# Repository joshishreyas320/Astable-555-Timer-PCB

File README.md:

# Astable 555 Timer PCB

> Eagle CAD PCB Design | 2-Layer Board | NE555 + 7805

---

## Project Description
A variable-frequency astable oscillator PCB designed in **Eagle CAD** using the classic **NE555 timer IC** in astable mode. A **100kΩ potentiometer** allows real-time frequency adjustment. Input power (+12V) is regulated to +5V using a **7805 linear regulator**. An LED blinks at the output frequency for visual feedback. The board includes a DC barrel jack and a 2-pin power header for flexible power input.

**Short Description (≤350 chars):**
> Astable 555 timer PCB with variable frequency output using 100kΩ potentiometer. NE555 IC generates continuous square wave with LED indicator. 12V input regulated via 7805. Designed in Eagle CAD.

---

## Key Components

| Component | Description |
|-----------|-------------|
| **NE555** | Timer IC in astable (free-running oscillator) mode |
| **7805 (IC1)** | 5V linear voltage regulator (TO-92) |
| **R5 – 100kΩ POT** | Variable resistor for frequency tuning |
| **R1 – 10kΩ** | Timing resistor Ra |
| **R2 – 1kΩ** | Timing resistor Rb |
| **R3 – 330Ω** | LED current limiting resistor |
| **C3, C4 – 10µF** | Timing capacitor and supply filter |
| **C1, C2 – 0.1µF** | Bypass/decoupling capacitors |
| **LED1** | Output frequency visual indicator |
| **DC JACK** | 2.0mm barrel jack for power input |

---

## Design Features
- NE555 wired in astable mode for continuous square wave output
- 100kΩ potentiometer enables real-time frequency adjustment
- Frequency approximately: f = 1.44 / ((R1 + 2×R2 + POT) × C3)
- 12V DC input regulated to stable 5V via 7805 regulator
- LED blinks at oscillator frequency – instant visual verification
- Dual power input: DC barrel jack + 2-pin pin header
- All through-hole components for easy soldering and prototyping

---

## Signal Flow
```
DC Barrel Jack / JP1 Header – 12V Input
       ↓
  7805 – 5V Voltage Regulator
       ↓
  NE555 Timer IC – Astable Mode
       ↑
  R1 (10kΩ) + R2 (1kΩ) + R5 POT (100kΩ) + C3 (10µF) – RC Timing
       ↓
  Square Wave Output (Pin 3)
       ↓
  R3 (330Ω) + LED1 – Visual Output Indicator
```

---

## Files Included
- Astable_555_timer.sch – Eagle Schematic
- Astable_555_timer.brd – Eagle PCB Layout
- GERBER_FILES_Astable_555_timer_2026-05-20.zip – Gerber files

---

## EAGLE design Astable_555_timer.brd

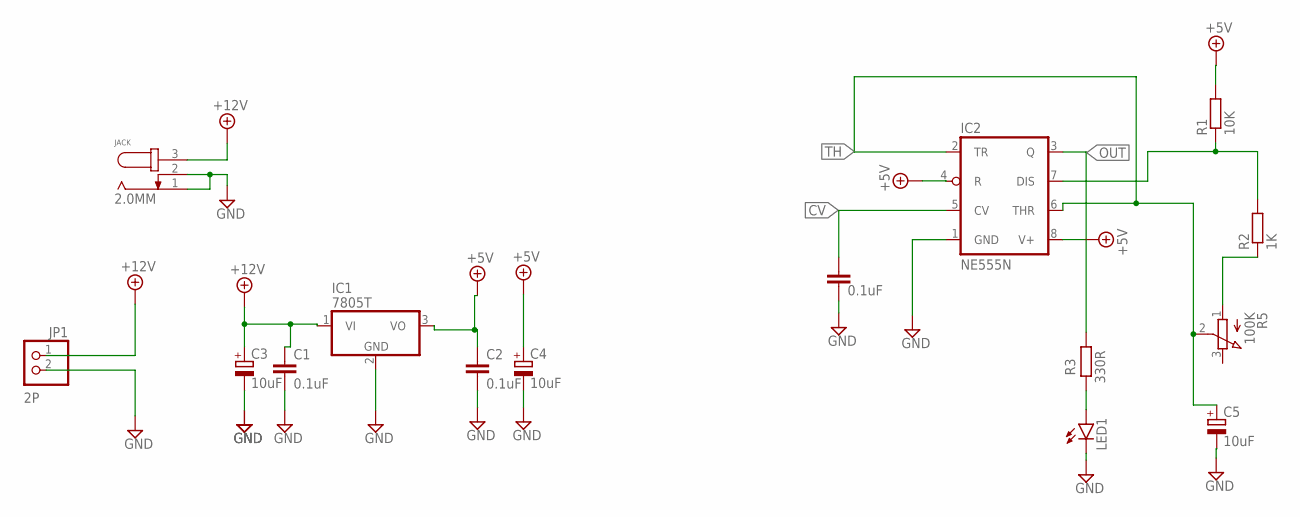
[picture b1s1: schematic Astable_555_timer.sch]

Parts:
C1, C2, C6: 0.1uF; C050-030X075
C3, C4, C5: 10uF; E3,5-8
IC1: 7805T; TO220H
IC2: NE555N; DIL08
JACK: 2.0MM; SPC4078
JP1: 2P; 1X02
LED1: LED5MM
R1: 10K; 0207/10
R2: 1K; 0207/10
R3: 330R; 0207/10
R5: 100K; 3RP/1610N

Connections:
+5V: C2.1, C4.+, IC1.3 (VO), IC2.4 (R), IC2.8 (V+), R1.2
+12V: C1.1, C3.+, IC1.1 (VI), JACK.3, JP1.1
CV: C6.1, IC2.5 (CV)
GND: C1.2, C2.2, C3.-, C4.-, C5.-, C6.2, IC1.2 (GND), IC2.1 (GND), JACK.1, JACK.2, JP1.2, LED1.K (C)
unnamed: R2.1, R5.1 (A)
unnamed: IC2.7 (DIS), R1.1, R2.2
unnamed: LED1.A, R3.1
OUT: IC2.3 (Q), R3.2
TH: C5.+, IC2.2 (TR), IC2.6 (THR), R5.2 (S)

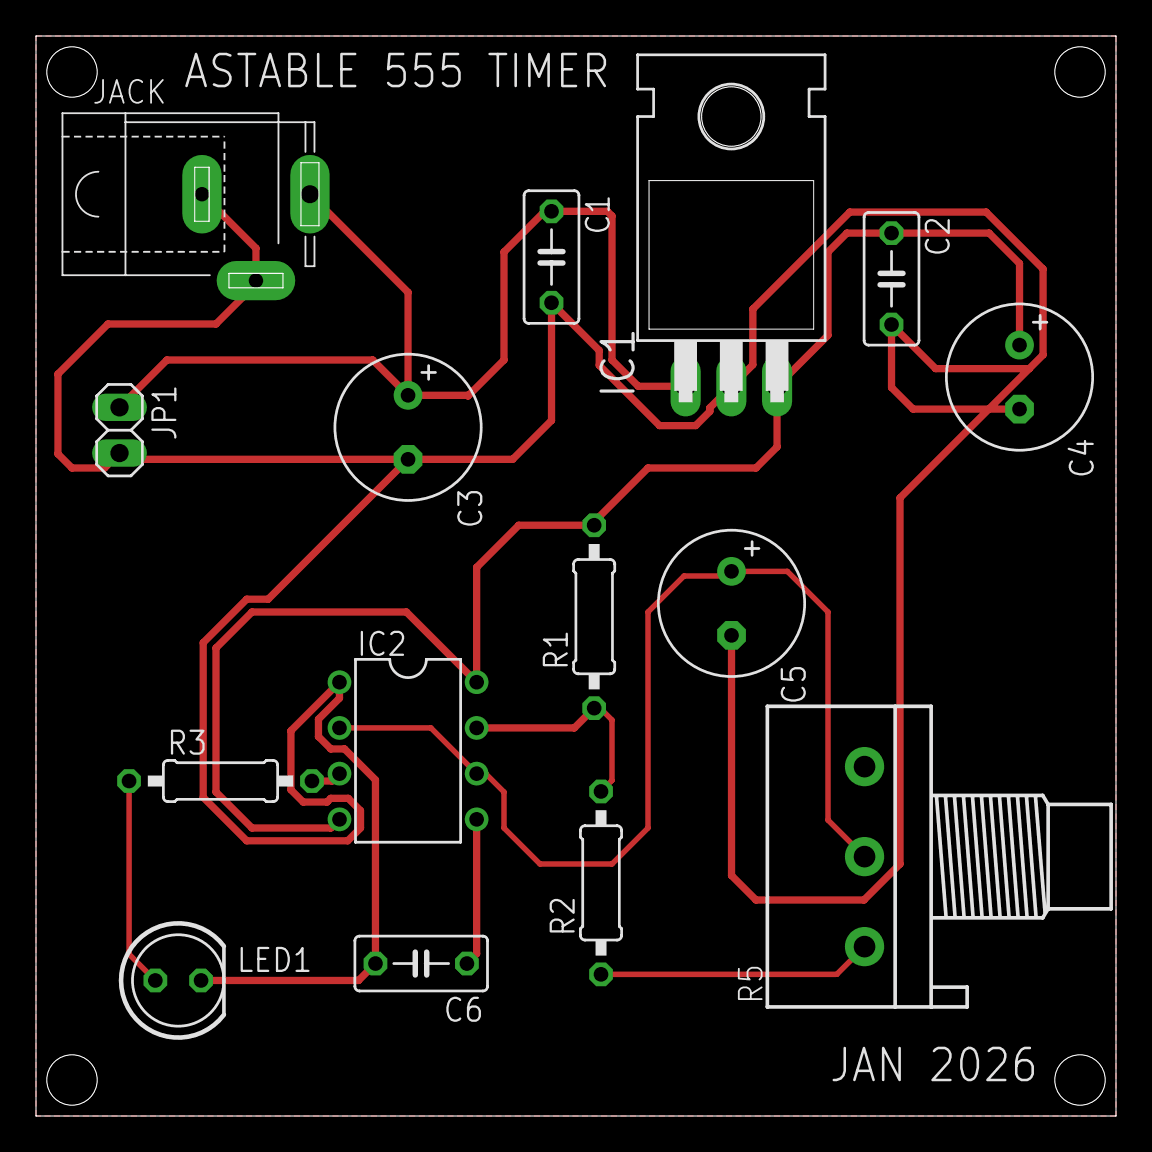
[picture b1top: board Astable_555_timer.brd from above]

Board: 2 copper layers, 60.0 x 60.0 mm, 15 parts (0 on the bottom side), 9 nets.

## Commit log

2026-06-06 Enhance README with project details and specifications
    Updated README with detailed project description, key components, design features, signal flow, and included files.
